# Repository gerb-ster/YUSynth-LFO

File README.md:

# YUSynth LFO

I'm working on some new modules, one of them is this VC-LFO adaptation from YUSynth. As far as I can determine this is a VCO that generates a saw waveform which is then run thru some wave shapers to create a saw, tri, pulse and sine wave.

I've made some modifications:

- I've powered it with +/- 12v instead of the +/- 15v.
- I've ommited the range switch section, after breadboarding it I found the range with the 1 uF cap quite sufficient.
- I also changed some resistor values to make sure the output is 10vpp around 0v for all waveforms.
- I rearranged the wave shapers a bit; the tri/sine section comes after the saw buffer, this way the tri/sine section outputs a 10vpp around 0v without the need for extra components.

In the YUSynth design there was 1 unused op-amp section; I've used that one to invert the saw into an extra ramp output.

The original design:
http://yusynth.net/Modular/EN/LFO/VC-LFO2.html

## Status: Work in Progress

- done: first schematic & board design
- done: breadboard and test
- done: design frontpanel
- todo: order PCB and build prototype

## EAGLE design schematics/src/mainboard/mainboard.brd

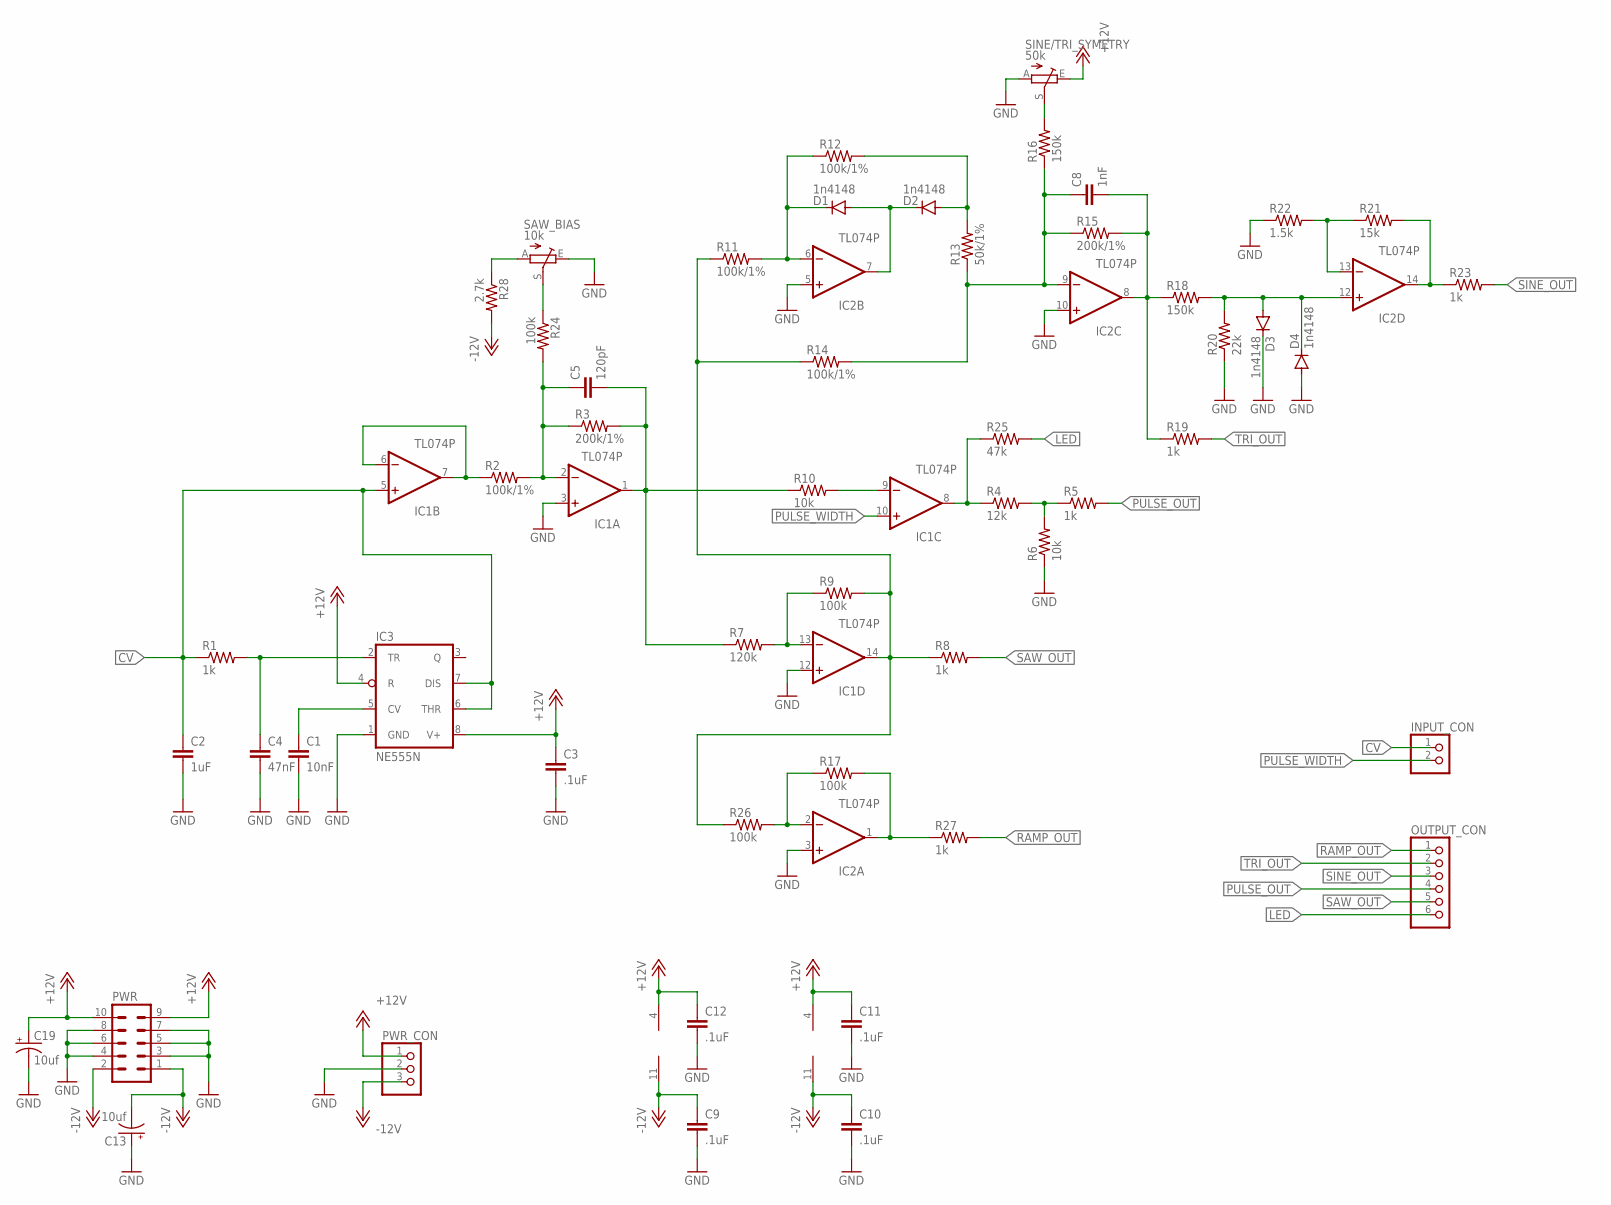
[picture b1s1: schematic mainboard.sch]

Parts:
C1: 10nF; C050-024X044
C2: 1uF; C075-032X103
C3, C9, C10, C11, C12: .1uF; C050-024X044
C4: 47nF; C050-024X044
C5: 120pF; C050-024X044
C8: 1nF; C050-024X044
C13, C19: 10uf; E2,5-5
D1, D2, D3, D4: 1n4148; DO35-7
IC1, IC2: TL074P; DIL14
IC3: NE555N; DIL08
INPUT_CON: PINHD-1X2; 1X02
OUTPUT_CON: PINHD-1X6; 1X06
PWR: ML10
PWR_CON: PINHD-1X3; 1X03
R1, R5, R8, R19, R23, R27: 1k; 0207/7
R2, R11, R12, R14: 100k/1%; 0207/7
R3, R15: 200k/1%; 0207/7
R4: 12k; 0207/7
R6, R10: 10k; 0207/7
R7: 120k; 0207/7
R9, R17, R24, R26: 100k; 0207/7
R13: 50k/1%; 0207/7
R16, R18: 150k; 0207/7
R20: 22k; 0207/7
R21: 15k; 0207/7
R22: 1.5k; 0207/7
R25: 47k; 0207/7
R28: 2.7k; 0207/7
SAW_BIAS: 10k; S64YW
SINE/TRI_SYMETRY: 50k; S64YW

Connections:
+12V: C3.1, C11.1, C12.1, C19.+, IC1.4 (V+), IC2.4 (V+), IC3.4 (R), IC3.8 (V+), PWR.9, PWR.10, PWR_CON.1, SINE/TRI_SYMETRY.E
-12V: C9.1, C10.1, C13.-, IC1.11 (V-), IC2.11 (V-), PWR.1, PWR.2, PWR_CON.3, R28.2
CV: C2.1, IC1.5 (+IN), IC3.6 (THR), IC3.7 (DIS), INPUT_CON.1, R1.1
GND: C1.2, C2.2, C3.2, C4.2, C9.2, C10.2, C11.2, C12.2, C13.+, C19.-, D3.C, D4.A, IC1.3 (+IN), IC1.12 (+IN), IC2.3 (+IN), IC2.5 (+IN), IC2.10 (+IN), IC3.1 (GND), PWR.3, PWR.4, PWR.5, PWR.6, PWR.7, PWR.8, PWR_CON.2, R6.1, R20.1, R22.1, SAW_BIAS.E, SINE/TRI_SYMETRY.A
LED: OUTPUT_CON.6, R25.2
LED_OUT: IC1.8 (OUT), R4.1, R25.1
unnamed: C1.1, IC3.5 (CV)
unnamed: C4.1, IC3.2 (TR), R1.2
unnamed: IC1.6 (-IN), IC1.7 (OUT), R2.1
unnamed: C5.1, IC1.2 (-IN), R2.2, R3.1, R24.2
unnamed: IC2.2 (-IN), R17.1, R26.2
unnamed: R4.2, R5.1, R6.2
unnamed: R24.1, SAW_BIAS.S
unnamed: C5.2, IC1.1 (OUT), R3.2, R7.1, R10.1
unnamed: IC1.13 (-IN), R7.2, R9.1
unnamed: R28.1, SAW_BIAS.A
unnamed: IC1.9 (-IN), R10.2
unnamed: D1.C, IC2.6 (-IN), R11.2, R12.1
unnamed: C8.1, IC2.9 (-IN), R13.1, R14.2, R15.1, R16.1
unnamed: D1.A, D2.C, IC2.7 (OUT)
unnamed: D2.A, R12.2, R13.2
unnamed: R16.2, SINE/TRI_SYMETRY.S
unnamed: C8.2, IC2.8 (OUT), R15.2, R18.1, R19.1
unnamed: D3.A, D4.C, IC2.12 (+IN), R18.2, R20.2
unnamed: IC2.14 (OUT), R21.2, R23.1
unnamed: IC2.13 (-IN), R21.1, R22.2
unnamed: IC1.14 (OUT), R8.1, R9.2, R11.1, R14.1, R26.1
unnamed: IC2.1 (OUT), R17.2, R27.1
PULSE_OUT: OUTPUT_CON.4, R5.2
PULSE_WIDTH: IC1.10 (+IN), INPUT_CON.2
RAMP_OUT: OUTPUT_CON.1, R27.2
SAW_OUT: OUTPUT_CON.5, R8.2
SINE_OUT: OUTPUT_CON.3, R23.2
TRI_OUT: OUTPUT_CON.2, R19.2

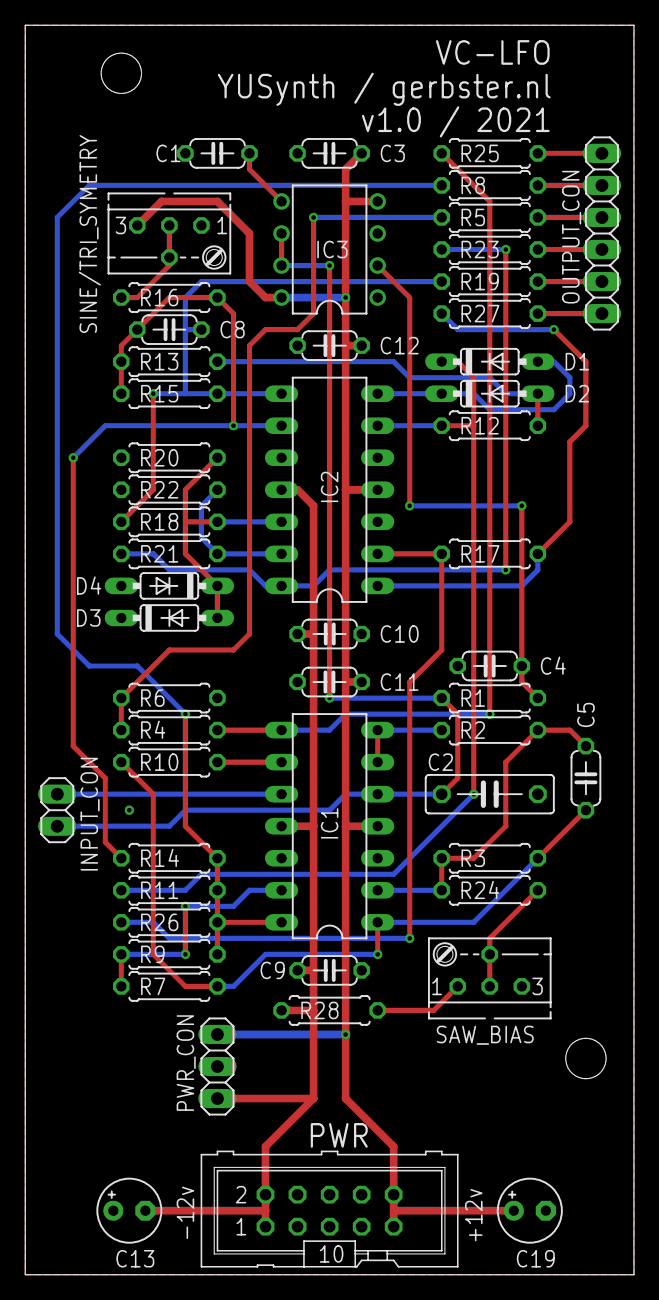
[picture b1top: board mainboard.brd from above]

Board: 2 copper layers, 48.3 x 99.1 mm, 53 parts (0 on the bottom side), 34 nets.

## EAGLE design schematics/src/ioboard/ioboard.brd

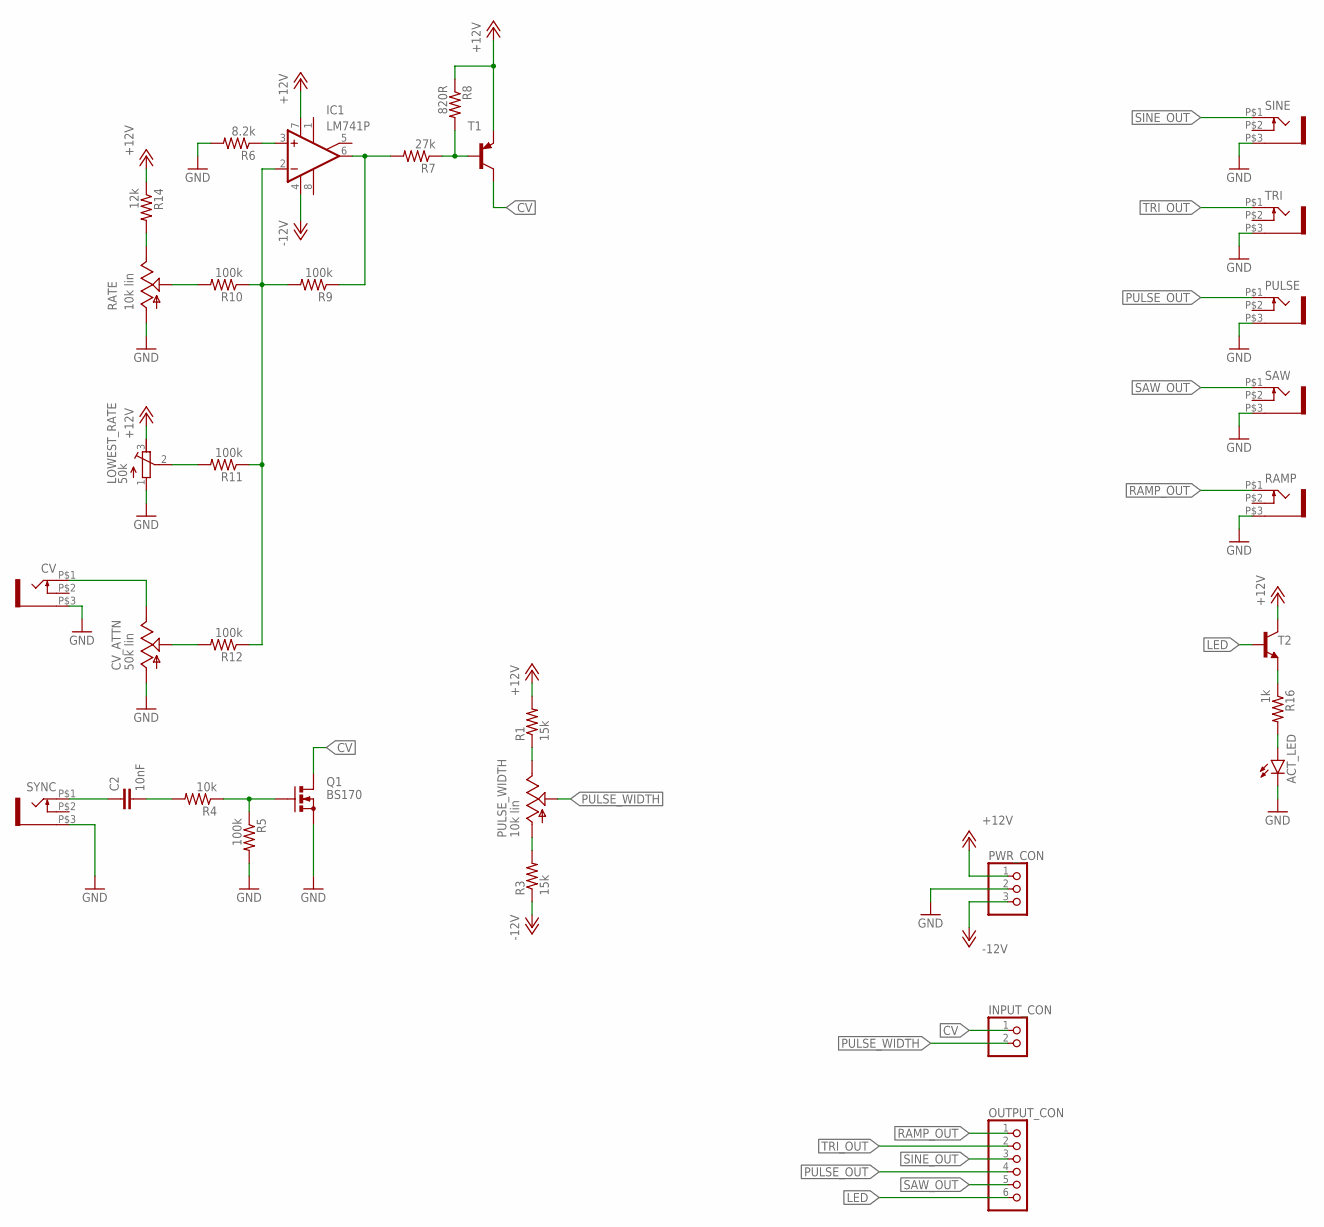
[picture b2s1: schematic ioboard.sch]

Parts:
ACT_LED: LED5MM
C2: 10nF; C050-024X044
CV: WQP-PJ301M-12_JACK
CV_ATTN: 50k lin; EVUF
IC1: LM741P; DIL08
INPUT_CON: PINHD-1X2; 1X02
LOWEST_RATE: 50k; RTRIM64X
OUTPUT_CON: PINHD-1X6; 1X06
PULSE: WQP-PJ301M-12_JACK
PULSE_WIDTH: 10k lin; EVUF
PWR_CON: PINHD-1X3; 1X03
Q1: BS170; SOT54E
R1, R3: 15k; 0207/7
R4: 10k; 0207/7
R5, R9, R10, R11, R12: 100k; 0207/7
R6: 8.2k; 0207/7
R7: 27k; 0207/7
R8: 820R; 0207/7
R14: 12k; 0207/7
R16: 1k; 0207/7
RAMP: WQP-PJ301M-12_JACK
RATE: 10k lin; EVUF
SAW: WQP-PJ301M-12_JACK
SINE: WQP-PJ301M-12_JACK
SYNC: WQP-PJ301M-12_JACK
T1: BC557C-PNP-TO92-EBC; TO92-EBC
T2: BC547-NPN-TO92-CBE; TO92-CBE
TRI: WQP-PJ301M-12_JACK

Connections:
+12V: IC1.7 (V+), LOWEST_RATE.3 (E), PWR_CON.1, R1.2, R8.1, R14.1, T1.E, T2.C
-12V: IC1.4 (V-), PWR_CON.3, R3.1
CV: INPUT_CON.1, Q1.D, T1.C
GND: ACT_LED.K (C), CV.P$3 (1), CV_ATTN.1 (A), LOWEST_RATE.1 (A), PULSE.P$3 (1), PWR_CON.2, Q1.S, R5.2, R6.2, RAMP.P$3 (1), RATE.1 (A), SAW.P$3 (1), SINE.P$3 (1), SYNC.P$3 (1), TRI.P$3 (1)
LED: OUTPUT_CON.6, T2.B
unnamed: PULSE_WIDTH.1 (A), R3.2
unnamed: PULSE_WIDTH.3 (E), R1.1
unnamed: C2.1, SYNC.P$1 (2)
unnamed: C2.2, R4.2
unnamed: Q1.G, R4.1, R5.1
unnamed: IC1.3 (+IN), R6.1
unnamed: IC1.6 (OUT), R7.2, R9.1
unnamed: R7.1, R8.2, T1.B
unnamed: R14.2, RATE.3 (E)
unnamed: R10.2, RATE.2 (S)
unnamed: IC1.2 (-IN), R9.2, R10.1, R11.1, R12.1
unnamed: LOWEST_RATE.2 (S), R11.2
unnamed: CV_ATTN.2 (S), R12.2
unnamed: CV.P$1 (2), CV_ATTN.3 (E)
unnamed: R16.1, T2.E
unnamed: ACT_LED.A, R16.2
PULSE_OUT: OUTPUT_CON.4, PULSE.P$1 (2)
PULSE_WIDTH: INPUT_CON.2, PULSE_WIDTH.2 (S)
RAMP_OUT: OUTPUT_CON.1, RAMP.P$1 (2)
SAW_OUT: OUTPUT_CON.5, SAW.P$1 (2)
SINE_OUT: OUTPUT_CON.3, SINE.P$1 (2)
TRI_OUT: OUTPUT_CON.2, TRI.P$1 (2)

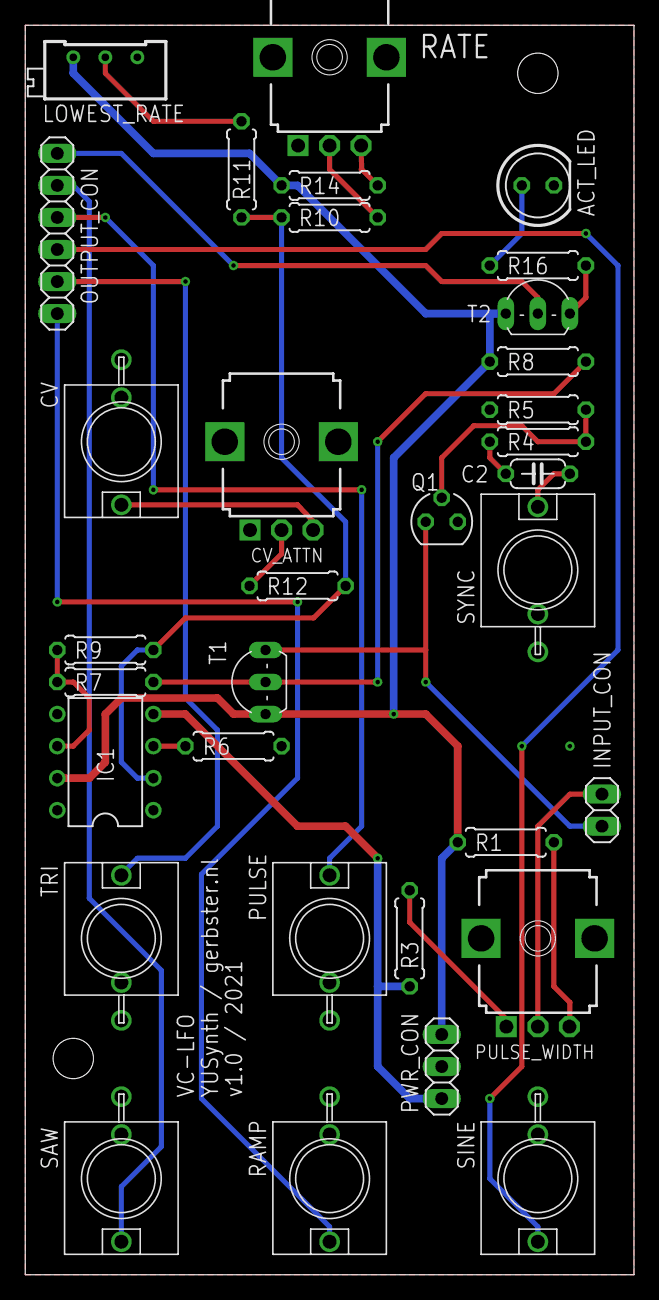
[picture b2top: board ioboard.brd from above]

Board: 2 copper layers, 48.3 x 99.1 mm, 33 parts (0 on the bottom side), 27 nets.

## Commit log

2021-05-06 initial designs
2021-05-06 project documentation
2021-05-07 Added files & structure
2021-05-10 Added Status
2021-05-11 Added Status & Images
2021-06-15 Updated Schematics, Fixed Power Socket orientation
2021-07-19 Fixed minor issues, added documentation and updated some faceplates
2021-08-06 Updated some schematics and docs
2021-08-10 Fixed some bugs and updated documentation
2022-04-20 Some updates & bugfixes
2022-04-22 Fixed schematics & descriptions
2022-05-17 Updated Firmware
2022-05-18 Updated Faceplates
2022-05-18 Fixed issues
2022-05-21 Fixed schematics
2022-05-28 General updates
2022-06-13 Faceplates & Bugfixes
2022-06-26 Fixed faceplate design
